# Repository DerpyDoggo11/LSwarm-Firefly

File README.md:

# LSwarm Firefly
A single motor Micro-Aerial Vehicle for drone swarm light displays

## Case

## 3D PCB Preview

## PCB Wiring

## PCB Schematic

### Download ./latestProduction to fabricate your own PCB.

## Introduction
The LS Firefly is the baby brother to the original [LS Mk.1](https://github.com/DerpyDoggo11/LSwarm), the goal is to be smaller, safer, and a little more unique than the previous drone. Although it does come at some costs such as reduced manuverability and no USB-C connectivity. Like the previous model, rather than using GPS, it uses UWB frequencies to communicate with ground anchors (see [LS Anchor](https://github.com/DerpyDoggo11/LSwarm-Anchor)) for positioning. To fabricate these drones yourself, see the bill of materials below and follow the instructions. 

Note: this drone is all open sourced under the GNU GPL license! (do what you will with the code and designs but make sure to keep it open-source! :D)

### Are drone swarms legal in the US?
TLDR: yes and no, mostly no but sometimes yes. 

In the US, flying more than one drone by yourself outside is technically not legal without a permit, but flying indoors (or under some netting outside) is perfectly allowed, so make sure you understand this before buying or assembling any components.

If you live outside of the US, the restrictions will be different so make sure you check with your local government. 

## Bill of Materials 

### (Minimum build for testing: 5 drones)

| Quantity | Components | Price | Link |
|--------- |----------|----------| -----|
| 5  | Brushless Motors | ~$56.27  | [here](https://www.aliexpress.us/item/3256811751884831.html?spm=a2g0o.productlist.main.5.4bc27ec1sXcpi9&algo_pvid=f93d3c7b-d188-41d3-8071-ca4f01f3da9e&algo_exp_id=f93d3c7b-d188-41d3-8071-ca4f01f3da9e-4&pdp_ext_f=%7B%22order%22%3A%2244%22%2C%22eval%22%3A%221%22%2C%22fromPage%22%3A%22search%22%7D&pdp_npi=6%40dis%21USD%2127.91%2112.75%21%21%2127.91%2112.75%21%402103129f17839010468456329ea712%2112000057077353974%21sea%21US%217493938711%21X%211%210%21n_tag%3A-29919%3Bd%3Ad260408f%3Bm03_new_user%3A-29895%3BpisId%3A5000000204411062&curPageLogUid=VGuc6eNMjhlE&utparam-url=scene%3Asearch%7Cquery_from%3A%7Cx_object_id%3A1005011938199583%7C_p_origin_prod%3A#nav-review)
| 5 | 65mm Propellers (1.5mm hole) | $2.42 | [here](https://www.aliexpress.us/item/3256808528649872.html?spm=a2g0o.productlist.main.1.b0be6fedKhbLdF&algo_pvid=3254f102-23a3-44f5-862f-50a3a50c42db&algo_exp_id=3254f102-23a3-44f5-862f-50a3a50c42db-0&pdp_ext_f=%7B%22order%22%3A%2263%22%2C%22eval%22%3A%221%22%2C%22fromPage%22%3A%22search%22%7D&pdp_npi=6%40dis%21USD%213.73%210.99%21%21%213.73%210.99%21%402101e80f17839019729517303e1028%2112000046361007970%21sea%21US%217493938711%21X%211%210%21n_tag%3A-29919%3Bd%3Ad260408f%3Bm03_new_user%3A-29895%3BpisId%3A5000000204411062&curPageLogUid=khfzd3PNDSbd&utparam-url=scene%3Asearch%7Cquery_from%3A%7Cx_object_id%3A1005008714964624%7C_p_origin_prod%3A) 
| 10  | 1s 300mAh Battery | ~$19.75 | [here](https://www.aliexpress.us/item/3256801127609470.html?spm=a2g0o.productlist.main.8.43a2a5M9a5M9yu&aem_p4p_detail=202607121047491621817576276750009408507&algo_pvid=07c6ddd0-7cad-4da9-88c7-c570960c9574&algo_exp_id=07c6ddd0-7cad-4da9-88c7-c570960c9574-7&pdp_ext_f=%7B%22order%22%3A%22137%22%2C%22eval%22%3A%221%22%2C%22fromPage%22%3A%22search%22%7D&pdp_npi=6%40dis%21USD%214.71%213.30%21%21%2131.79%2122.25%21%40210319b017838784692687812e95b8%2112000015664187048%21sea%21US%217493938711%21X%211%210%21n_tag%3A-29919%3Bd%3Ad260408f%3Bm03_new_user%3A-29895&curPageLogUid=hyAg3GWOKWbh&utparam-url=scene%3Asearch%7Cquery_from%3A%7Cx_object_id%3A1005001313924222%7C_p_origin_prod%3A&search_p4p_id=202607121047491621817576276750009408507_2) 
|5 | 2.4G Wifi Antennas | ~$3.52 | [here](https://www.aliexpress.us/item/3256802833801038.html?spm=a2g0o.productlist.main.17.44bbCrBdCrBdFl&algo_pvid=20d56933-2b0c-45d5-8601-1bc6a9682401&algo_exp_id=20d56933-2b0c-45d5-8601-1bc6a9682401-16&pdp_ext_f=%7B%22order%22%3A%221074%22%2C%22eval%22%3A%221%22%2C%22fromPage%22%3A%22search%22%7D&pdp_npi=6%40dis%21USD%213.55%213.52%21%21%213.55%213.52%21%402101ef5e17781321493642302e40a6%2112000023272348781%21sea%21US%217493938711%21X%211%210%21n_tag%3A-29913%3Bd%3A21b1ce8d%3Bm03_new_user%3A-29895&curPageLogUid=rLnZuf4b98Bi&utparam-url=scene%3Asearch%7Cquery_from%3A%7Cx_object_id%3A1005003020115790%7C_p_origin_prod%3A)
| 5  | LS Firefly PCBs | ~$25 (with shipping, cost can vary widely however) | Download repo, extract fabrication files, and fabricate pcb through JLCPCB, purchase components from LCSC (complete instructions for this may come soon)
| 5  | Electronics | ~$125 (with shipping, cost can vary widely however) | Purchase components from LCSC

Total cost: **$231,96**

Cost per drone: **$46.39**

## Tools / Other parts:
- Hot-air reflow station or SMD hot plate
- Soldering iron + solder
- Solder paste for SMD components
- Tweezers for SMD components

For drone light displays, you'll also need the [UWB anchors](https://github.com/DerpyDoggo11/LSwarm-Anchor) and a powerful MCU devboard or laptop.

## Assembly:
1. Apply solder paste to all smd components directly or through a stencil
2. Heat up components with a hot plate or hot-air gun
3. 3D print drone case
4. Mount components to drone case
4. Plug in USB-C port and upload software

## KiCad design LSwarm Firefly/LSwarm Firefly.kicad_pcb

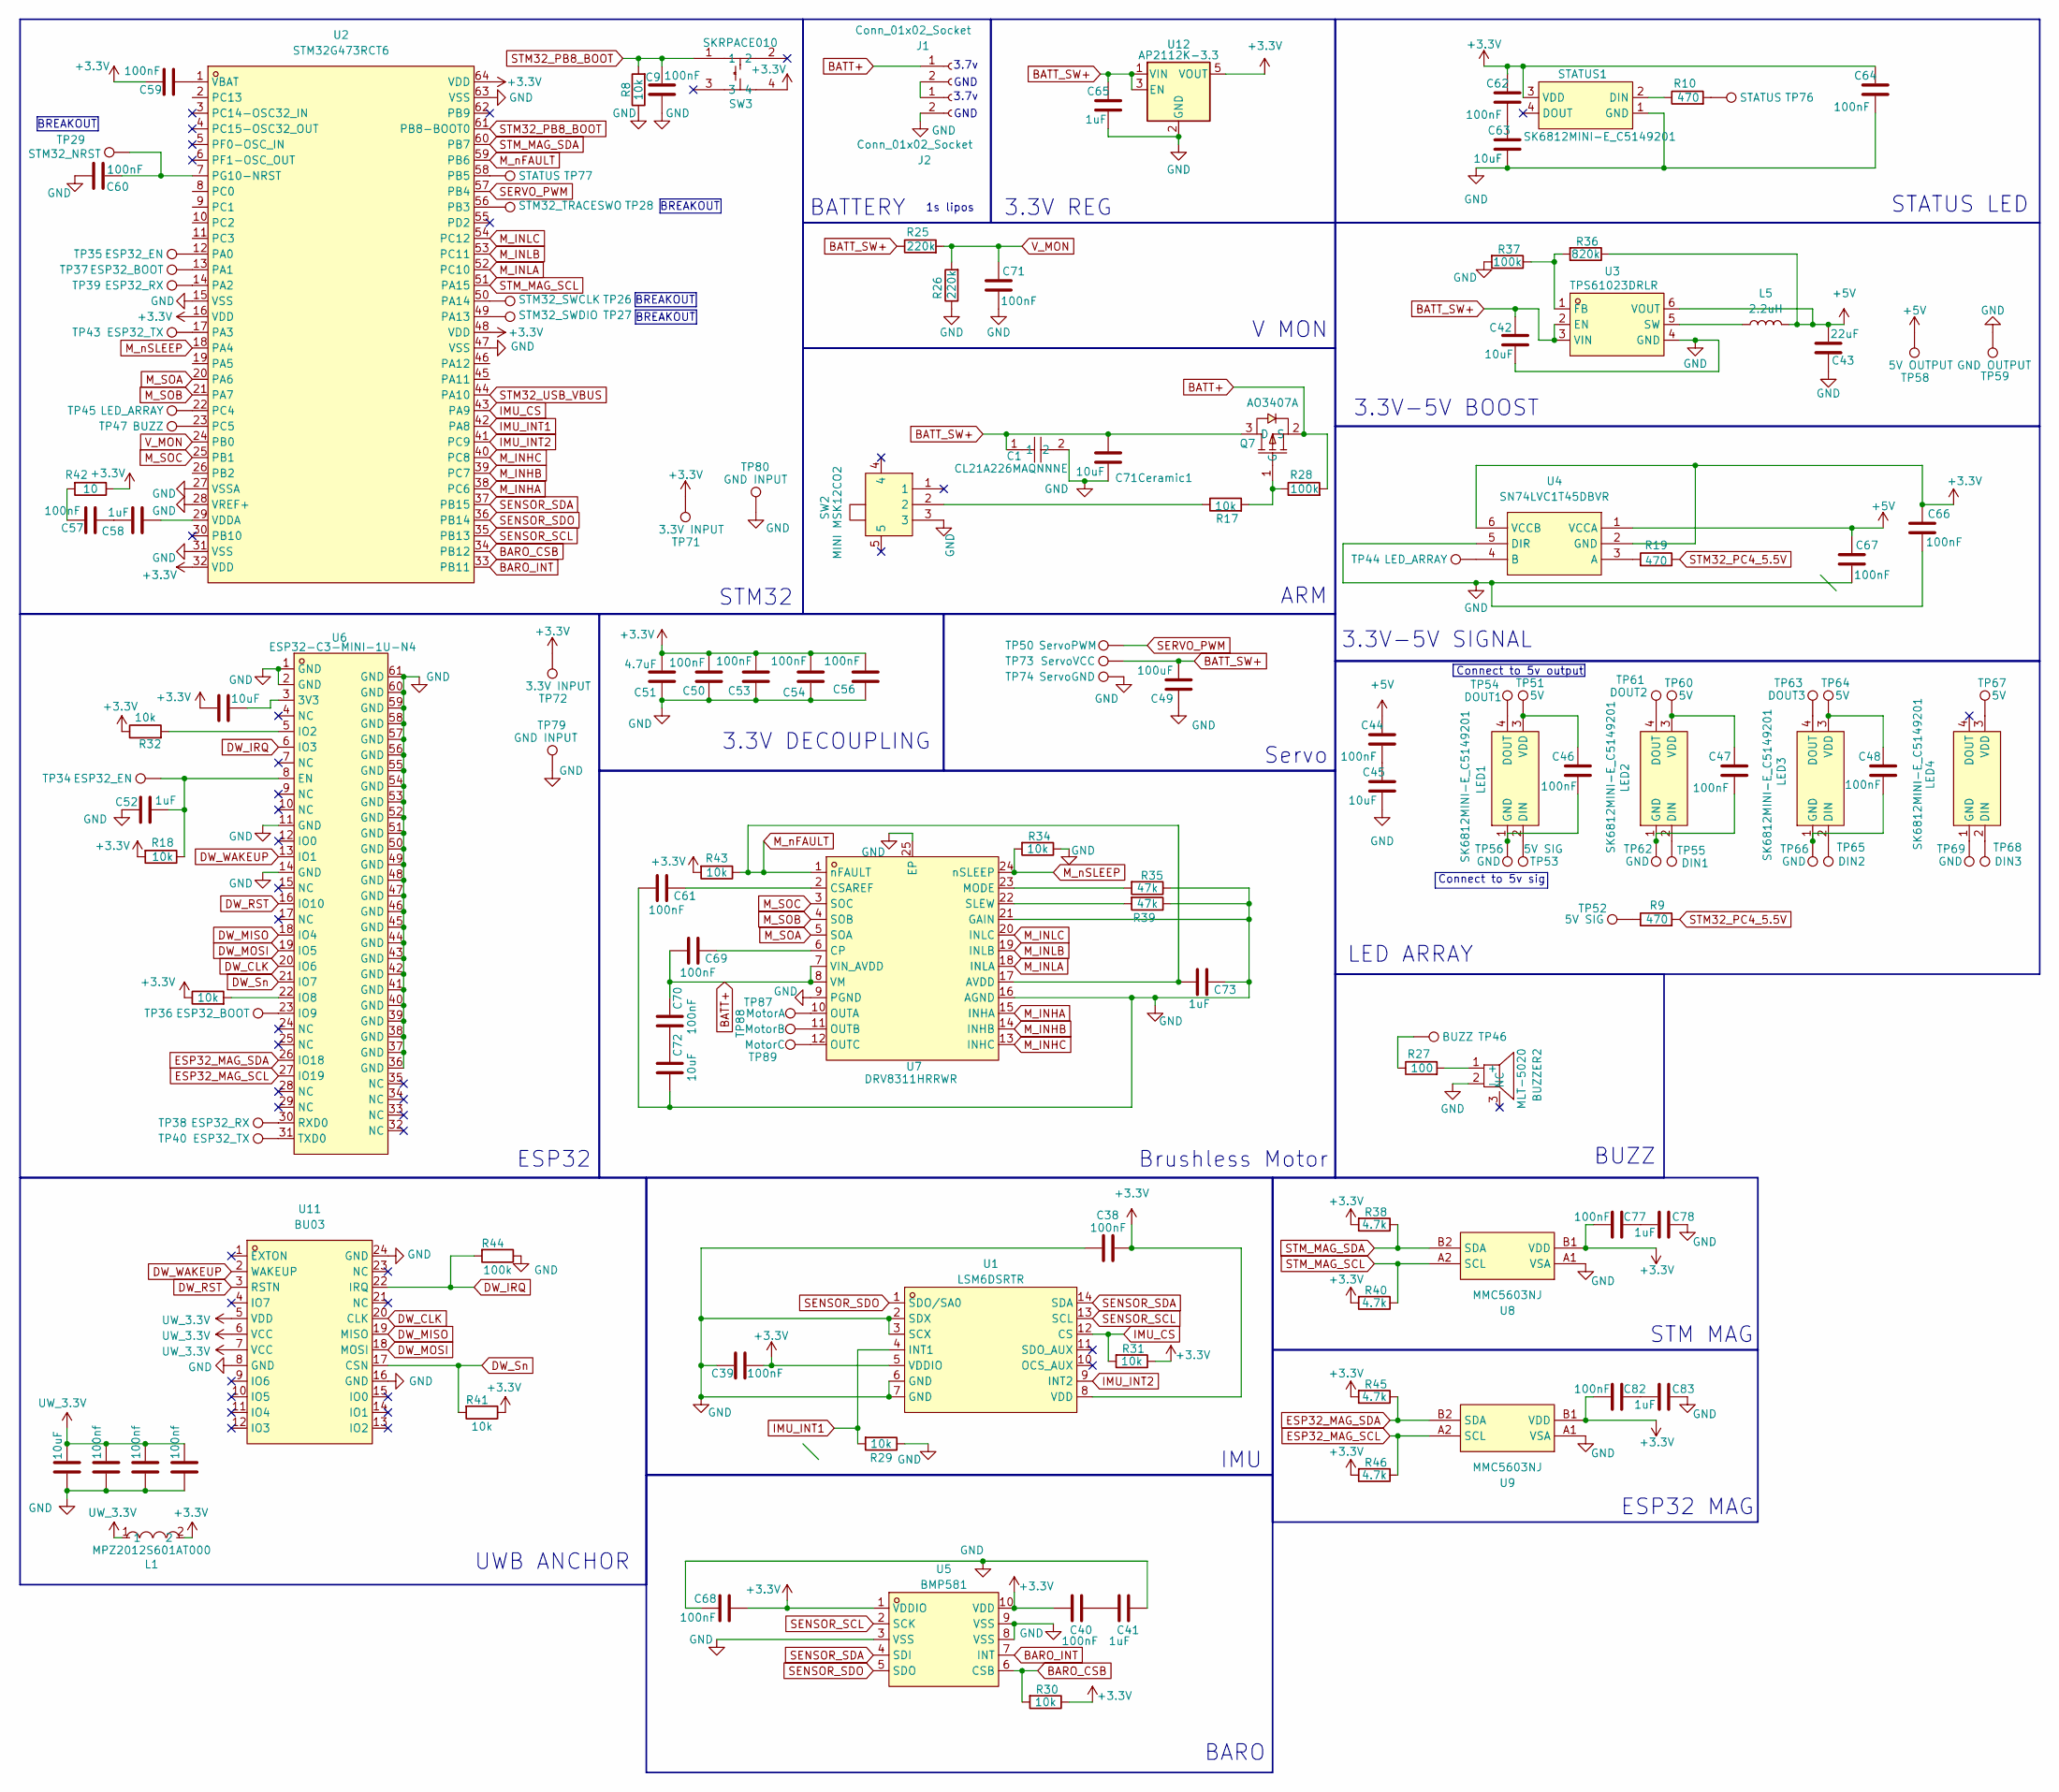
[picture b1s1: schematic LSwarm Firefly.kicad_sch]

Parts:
BUZZER2: MLT-5020; BUZ-SMD_L5.0-W5.5-P4.60; MPN MLT-5020; LCSC Part C94598
C1: CL21A226MAQNNNE; C0805; MPN CL21A226MAQNNNE; LCSC Part C45783
C9, C38, C39, C40, C44, C46, C47, C48, C50, C53, C54, C56, C57, C59, C60, C61, C62, C64, C66, C67, C68, C69, C70, C71, C77, C82: 100nF; C_0603_1608Metric
C41, C52, C58, C65, C73, C78, C83: 1uF; C_0603_1608Metric
C42, C45, C63, C71Ceramic1: 10uF; C_0805_2012Metric
C43: 22uF; C_0805_2012Metric
C49: 100uF; C_0603_1608Metric
C51: 4.7uF; C_0603_1608Metric
C55, C72, C76: 10uF; C_0603_1608Metric
C79, C80, C81: 100nf; C_0603_1608Metric
J1, J2: Conn_01x02_Socket; PinHeader_1x02_P1.00mm_Vertical
L1: MPZ2012S601AT000; L0805; MPN MPZ2012S601AT000; LCSC Part C21519
L5: 2.2uH; L_1210_3225Metric
LED1, LED2, LED3, LED4: SK6812MINI-E_C5149201; LED-SMD_4P-L3.2-W2.8-LS5.9_SK6812MINI-E; MPN SK6812MINI-E; LCSC Part C5149201
Q7: AO3407A; SOT-23-3_L2.9-W1.6-P1.90-LS2.8-BR; MPN AO3407A; LCSC Part C15155
R8, R17, R18, R29, R30, R31, R32, R33, R34, R41, R43: 10k; R_0603_1608Metric
R9, R10, R19: 470; R_0603_1608Metric
R25, R26: 220k; R_0603_1608Metric
R27: 100; R_0603_1608Metric
R28, R37, R44: 100k; R_0603_1608Metric
R35, R39: 47k; R_0603_1608Metric
R36: 820k; R_0603_1608Metric
R38, R40, R45, R46: 4.7k; R_0603_1608Metric
R42: 10; R_0603_1608Metric
STATUS1: SK6812MINI-E_C5149201; LED-SMD_4P-L3.2-W2.8-LS5.9_SK6812MINI-E; MPN SK6812MINI-E; LCSC Part C5149201
SW2: MINI MSK12CO2; SW-SMD_MSK12CO2; MPN MINI MSK12CO2; LCSC Part C2681570
SW3: SKRPACE010; KEY-SMD_4P-L4.2-W3.2-P2.20-LS4.6; MPN SKRPACE010; LCSC Part C139797
TP26: STM32_SWCLK; TestPoint_Pad_1.0x1.0mm
TP27: STM32_SWDIO; TestPoint_Pad_1.0x1.0mm
TP28: STM32_TRACESWO; TestPoint_Pad_1.0x1.0mm
TP29: STM32_NRST; TestPoint_Pad_1.0x1.0mm
TP34, TP35: ESP32_EN; TestPoint_Pad_1.0x1.0mm
TP36, TP37: ESP32_BOOT; TestPoint_Pad_1.0x1.0mm
TP38, TP39: ESP32_RX; TestPoint_Pad_1.0x1.0mm
TP40, TP43: ESP32_TX; TestPoint_Pad_1.0x1.0mm
TP44, TP45: LED_ARRAY; TestPoint_Pad_1.0x1.0mm
TP46, TP47: BUZZ; TestPoint_Pad_1.0x1.0mm
TP50: ServoPWM; TestPoint_Pad_1.0x1.0mm
TP51, TP60, TP64, TP67: 5V; TestPoint_Pad_1.0x1.0mm
TP52, TP53: 5V SIG; TestPoint_Pad_1.0x1.0mm
TP54: DOUT1; TestPoint_Pad_1.0x1.0mm
TP55: DIN1; TestPoint_Pad_1.0x1.0mm
TP56, TP62, TP66, TP69: GND; TestPoint_Pad_1.0x1.0mm
TP58: 5V OUTPUT; TestPoint_Pad_1.0x1.0mm
TP59: GND OUTPUT; TestPoint_Pad_1.0x1.0mm
TP61: DOUT2; TestPoint_Pad_1.0x1.0mm
TP63: DOUT3; TestPoint_Pad_1.0x1.0mm
TP65: DIN2; TestPoint_Pad_1.0x1.0mm
TP68: DIN3; TestPoint_Pad_1.0x1.0mm
TP71, TP72: 3.3V INPUT; TestPoint_Pad_1.0x1.0mm
TP73: ServoVCC; TestPoint_Pad_1.0x1.0mm
TP74: ServoGND; TestPoint_Pad_1.0x1.0mm
TP76, TP77: STATUS; TestPoint_Pad_1.0x1.0mm
TP79, TP80: GND INPUT; TestPoint_Pad_1.0x1.0mm
TP87: MotorA; TestPoint_Pad_1.0x1.0mm
TP88: MotorB; TestPoint_Pad_1.0x1.0mm
TP89: MotorC; TestPoint_Pad_1.0x1.0mm
U1: LSM6DSRTR; LGA-14_L3.0-W2.5-P0.50-BR; MPN LSM6DSRTR; LCSC Part C784817
U2: STM32G473RCT6; LQFP-64_L10.0-W10.0-P0.50-LS12.0-BL; MPN STM32G473RCT6; LCSC Part C529361
U3: TPS61023DRLR; SOT-563_L1.6-W1.2-P0.50-LS1.6-BR; MPN TPS61023DRLR; LCSC Part C919459
U4: SN74LVC1T45DBVR; SOT-23-6_L2.9-W1.6-P0.95-LS2.8-BR; MPN SN74LVC1T45DBVR; LCSC Part C7843
U5: BMP581; LGA-10_L2.0-W2.0-P0.50-TL_BMP581; MPN BMP581; LCSC Part C5362283
U6: ESP32-C3-MINI-1U-N4; WIFIM-SMD_61P-L13.2-W12.5-P0.80; MPN ESP32-C3-MINI-1U-N4; LCSC Part C2911374
U7: DRV8311HRRWR; QFN-24_L3.0-W3.0-P0.40-TL-EP1.9_TI_RRW0024A; MPN DRV8311HRRWR; LCSC Part C5218862
U8, U9: MMC5603NJ; FLIPCHIP-4_L0.8-W0.8-R2-C2-P0.40-TL; MPN MMC5603NJ; LCSC Part C404328
U11: BU03; WIRELM-SMD_BU03; MPN BU03; LCSC Part C42419011
U12: AP2112K-3.3; SOT-23-5

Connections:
+3.3V: C38.1, C39.1, C40.2, C50.2, C51.2, C53.2, C54.2, C55.2, C56.2, C59.1, C62.2, C64.2, C66.2, C68.1, C77.1, C82.1, L1.2, R18.2, R30.1, R31.1, R32.1, R33.1, R38.2, R40.2, R41.1, R42.1, R43.2, R45.2, R46.2, STATUS1.3 (VDD), SW3.4, TP71.1 (1_1), TP72.1 (1_1), U1.5 (VDDIO), U1.8 (VDD), U2.16 (VDD), U2.32 (VDD), U2.48 (VDD), U2.64 (VDD), U4.2 (GND), U4.6 (VCCB), U5.1 (VDDIO), U5.10 (VDD), U8.B1 (VDD), U9.B1 (VDD), U12.5 (VOUT)
+5V: C43.2, C44.2, C67.2, L5.2, R36.1, TP58.1 (1_1), U3.6 (VOUT), U4.1 (VCCA)
BARO_CSB: R30.2, U2.34 (PB12), U5.6 (CSB)
BARO_INT: U2.33 (PB11), U5.7 (INT)
BATT+: C69.2, C70.1, J1.1, Q7.2 (S), R28.2, U7.7 (VIN_AVDD), U7.8 (VM)
BATT_SW+: C1.1, C42.1, C49.2, C65.2, C71Ceramic1.2, Q7.3 (D), R25.1, TP73.1 (1_1), U3.2 (EN), U3.3 (VIN), U12.1 (VIN), U12.3 (EN)
DW_CLK: U6.20 (IO6), U11.20 (CLK)
DW_IRQ: R44.2, U6.6 (IO3), U11.22 (IRQ)
DW_MISO: U6.18 (IO4), U11.19 (MISO)
DW_MOSI: U6.19 (IO5), U11.18 (MOSI)
DW_RST: U6.16 (IO10), U11.3 (RSTN)
DW_Sn: R41.2, U6.21 (IO7), U11.17 (CSN)
DW_WAKEUP: U6.13 (IO1), U11.2 (WAKEUP)
ESP32_MAG_SCL: R46.1, U6.27 (IO19), U9.A2 (SCL)
ESP32_MAG_SDA: R45.1, U6.26 (IO18), U9.B2 (SDA)
GND: BUZZER2.2 (-), C1.2, C9.2, C38.2, C39.2, C41.1, C42.2, C43.1, C45.1, C49.1, C50.1, C51.1, C52.1, C53.1, C54.1, C56.1, C60.1, C61.2, C63.1, C64.1, C65.1, C66.1, C67.1, C68.2, C71.1, C71Ceramic1.1, C72.2, C73.1, C76.2, C78.2, C79.2, C80.2, C81.2, C83.2, J2.2, R8.1, R26.1, R29.1, R34.1, R35.1, R37.2, R39.1, R44.1, STATUS1.1 (GND), SW2.3, TP59.1 (1_1), TP74.1 (1_1), TP79.1 (1_1), TP80.1 (1_1), U1.2 (SDX), U1.3 (SCX), U1.6 (GND), U1.7 (GND), U2.15 (VSS), U2.27 (VSSA), U2.28 (VREF+), U2.31 (VSS), U2.47 (VSS), U2.63 (VSS), U3.4 (GND), U4.5 (DIR), U5.3 (VSS), U5.8 (VSS), U5.9 (VSS), U6.1 (GND), U6.2 (GND), U6.11 (GND), U6.14 (GND), U6.36 (GND), U6.37 (GND), U6.38 (GND), U6.39 (GND), U6.40 (GND), U6.41 (GND), U6.42 (GND), U6.43 (GND), U6.44 (GND), U6.45 (GND), U6.46 (GND), U6.47 (GND), U6.48 (GND), U6.49 (GND), U6.50 (GND), U6.51 (GND), U6.52 (GND), U6.53 (GND), U6.54 (GND), U6.55 (GND), U6.56 (GND), U6.57 (GND), U6.58 (GND), U6.59 (GND), U6.60 (GND), U6.61 (GND), U7.9 (PGND), U7.16 (AGND), U7.21 (GAIN), U7.25 (EP), U8.A1 (VSA), U9.A1 (VSA), U11.8 (GND), U11.16 (GND), U11.24 (GND), U12.2 (GND)
IMU_CS: R31.2, U1.12 (CS), U2.43 (PA9)
IMU_INT1: R29.2, U1.4 (INT1), U2.42 (PA8)
IMU_INT2: U1.9 (INT2), U2.41 (PC9)
M_INHA: U2.38 (PC6), U7.15 (INHA)
M_INHB: U2.39 (PC7), U7.14 (INHB)
M_INHC: U2.40 (PC8), U7.13 (INHC)
M_INLA: U2.52 (PC10), U7.18 (INLA)
M_INLB: U2.53 (PC11), U7.19 (INLB)
M_INLC: U2.54 (PC12), U7.20 (INLC)
M_SOA: U2.20 (PA6), U7.5 (SOA)
M_SOB: U2.21 (PA7), U7.4 (SOB)
M_SOC: U2.25 (PB1), U7.3 (SOC)
M_nFAULT: C73.2, R43.1, U2.59 (PB6), U7.1 (nFAULT), U7.17 (AVDD)
M_nSLEEP: R34.2, U2.18 (PA4), U7.24 (nSLEEP)
unnamed: BUZZER2.1 (+), R27.2
unnamed: C40.1, C41.2
unnamed: C44.1, C45.2
unnamed: C57.1, R42.2
unnamed: C57.2, C58.1
unnamed: C62.1, C63.2
unnamed: C70.2, C72.1
unnamed: C77.2, C78.1
unnamed: C82.2, C83.1
unnamed: J1.2, J2.1
unnamed: LED1.2 (DIN), TP53.1 (1_1)
unnamed: LED1.4 (DOUT), TP54.1 (1_1)
unnamed: C46.1, LED1.1 (GND), TP56.1 (1_1)
unnamed: C46.2, LED1.3 (VDD), TP51.1 (1_1)
unnamed: LED2.2 (DIN), TP55.1 (1_1)
unnamed: LED2.4 (DOUT), TP61.1 (1_1)
unnamed: C47.1, LED2.1 (GND), TP62.1 (1_1)
unnamed: C47.2, LED2.3 (VDD), TP60.1 (1_1)
unnamed: LED3.2 (DIN), TP65.1 (1_1)
unnamed: LED3.4 (DOUT), TP63.1 (1_1)
unnamed: C48.1, LED3.1 (GND), TP66.1 (1_1)
unnamed: C48.2, LED3.3 (VDD), TP64.1 (1_1)
unnamed: LED4.2 (DIN), TP68.1 (1_1)
unnamed: LED4.1 (GND), TP69.1 (1_1)
unnamed: LED4.3 (VDD), TP67.1 (1_1)
unnamed: Q7.1 (G), R17.2, R28.1
unnamed: R9.1, TP52.1 (1_1)
unnamed: R10.2, TP76.1 (1_1)
unnamed: R17.1, SW2.2
unnamed: R27.1, TP46.1 (1_1)
unnamed: R10.1, STATUS1.2 (DIN)
unnamed: TP35.1 (1_1), U2.12 (PA0)
unnamed: TP37.1 (1_1), U2.13 (PA1)
unnamed: TP39.1 (1_1), U2.14 (PA2)
unnamed: TP43.1 (1_1), U2.17 (PA3)
unnamed: TP27.1 (1_1), U2.49 (PA13)
unnamed: TP26.1 (1_1), U2.50 (PA14)
unnamed: TP28.1 (1_1), U2.56 (PB3)
unnamed: TP77.1 (1_1), U2.58 (PB5)
unnamed: TP45.1 (1_1), U2.22 (PC4)
unnamed: TP47.1 (1_1), U2.23 (PC5)
unnamed: C60.2, TP29.1 (1_1), U2.7 (PG10-NRST)
unnamed: C59.2, U2.1 (VBAT)
unnamed: C58.2, U2.29 (VDDA)
unnamed: R36.2, R37.1, U3.1 (FB)
unnamed: L5.1, U3.5 (SW)
unnamed: R19.2, U4.3 (A)
unnamed: TP44.1 (1_1), U4.4 (B)
unnamed: C55.1, U6.3 (3V3)
unnamed: C52.2, R18.1, TP34.1 (1_1), U6.8 (EN)
unnamed: R32.2, U6.5 (IO2)
unnamed: R33.2, U6.22 (IO8)
unnamed: TP36.1 (1_1), U6.23 (IO9)
unnamed: TP38.1 (1_1), U6.30 (RXD0)
unnamed: TP40.1 (1_1), U6.31 (TXD0)
unnamed: C69.1, U7.6 (CP)
unnamed: C61.1, U7.2 (CSAREF)
unnamed: R35.2, U7.23 (MODE)
unnamed: TP87.1 (1_1), U7.10 (OUTA)
unnamed: TP88.1 (1_1), U7.11 (OUTB)
unnamed: TP89.1 (1_1), U7.12 (OUTC)
unnamed: R39.2, U7.22 (SLEW)
SENSOR_SCL: U1.13 (SCL), U2.35 (PB13), U5.2 (SCK)
SENSOR_SDA: U1.14 (SDA), U2.37 (PB15), U5.4 (SDI)
SENSOR_SDO: U1.1 (SDO/SA0), U2.36 (PB14), U5.5 (SDO)
SERVO_PWM: TP50.1 (1_1), U2.57 (PB4)
STM32_PB8_BOOT: C9.1, R8.2, SW3.1, U2.61 (PB8-BOOT0)
STM32_PC4_5.5V: R9.2, R19.1
STM32_USB_VBUS: U2.44 (PA10)
STM_MAG_SCL: R40.1, U2.51 (PA15), U8.A2 (SCL)
STM_MAG_SDA: R38.1, U2.60 (PB7), U8.B2 (SDA)
UW_3.3V: C76.1, C79.1, C80.1, C81.1, L1.1, U11.5 (VDD), U11.6 (VCC), U11.7 (VCC)
V_MON: C71.2, R25.2, R26.2, U2.24 (PB0)

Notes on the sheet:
3.3V DECOUPLING
3.3V REG
BUZZ
BREAKOUT
GND
Connect to 5v output
Connect to 5v sig
STM32
STM MAG
3.7v
ESP32 MAG
BARO
1s lipos
ARM
Brushless Motor
3.3V-5V SIGNAL
3.3V-5V BOOST
LED ARRAY
Servo
V MON
STATUS LED
ESP32
UWB ANCHOR
BATTERY
IMU

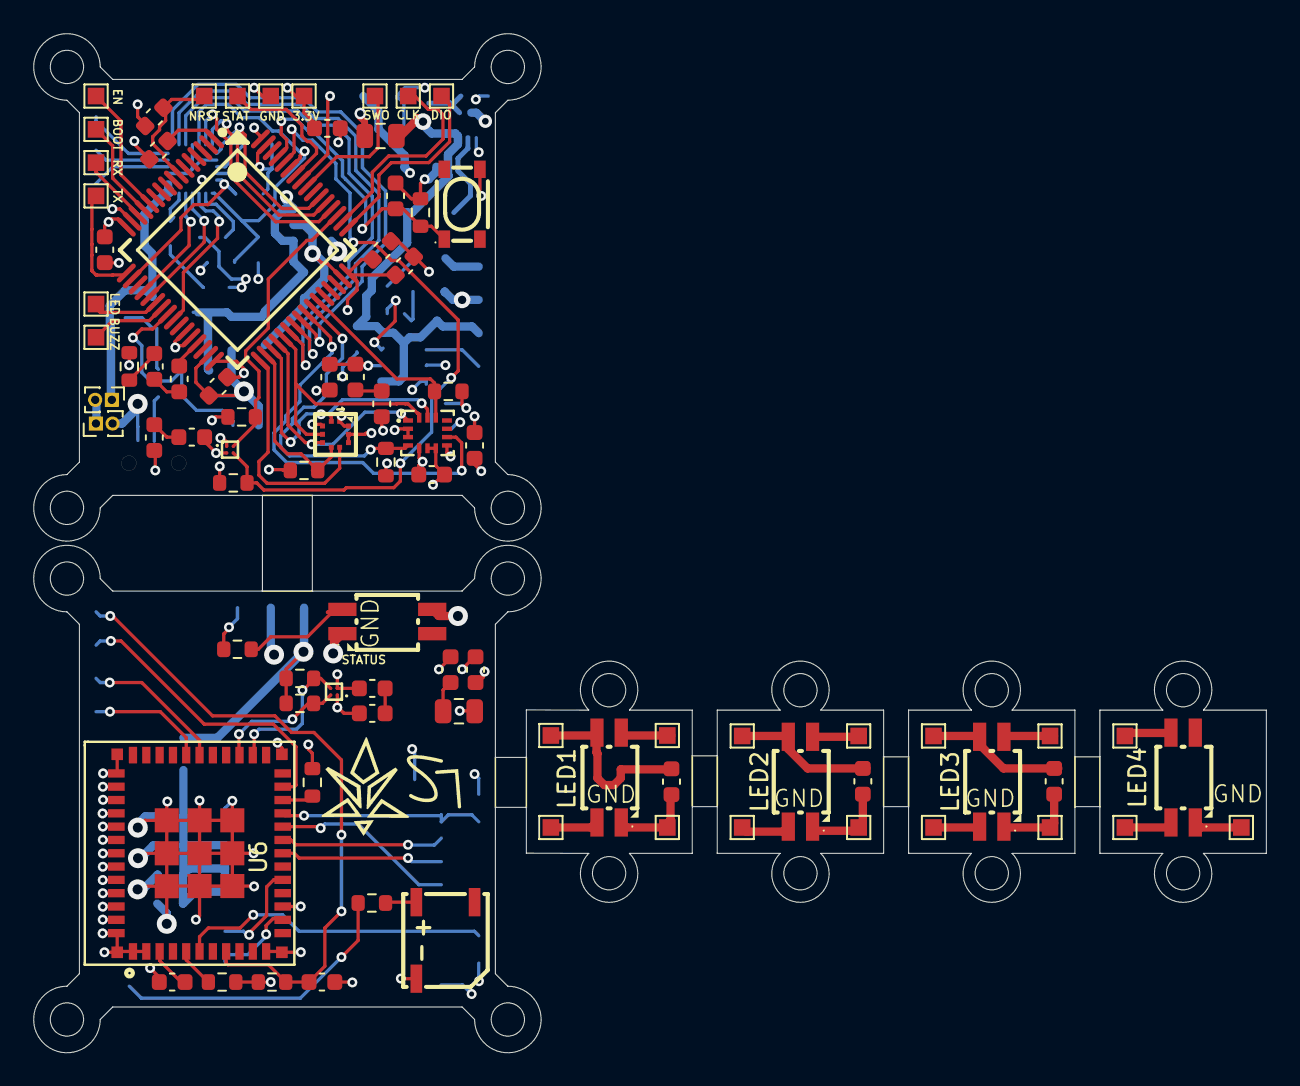
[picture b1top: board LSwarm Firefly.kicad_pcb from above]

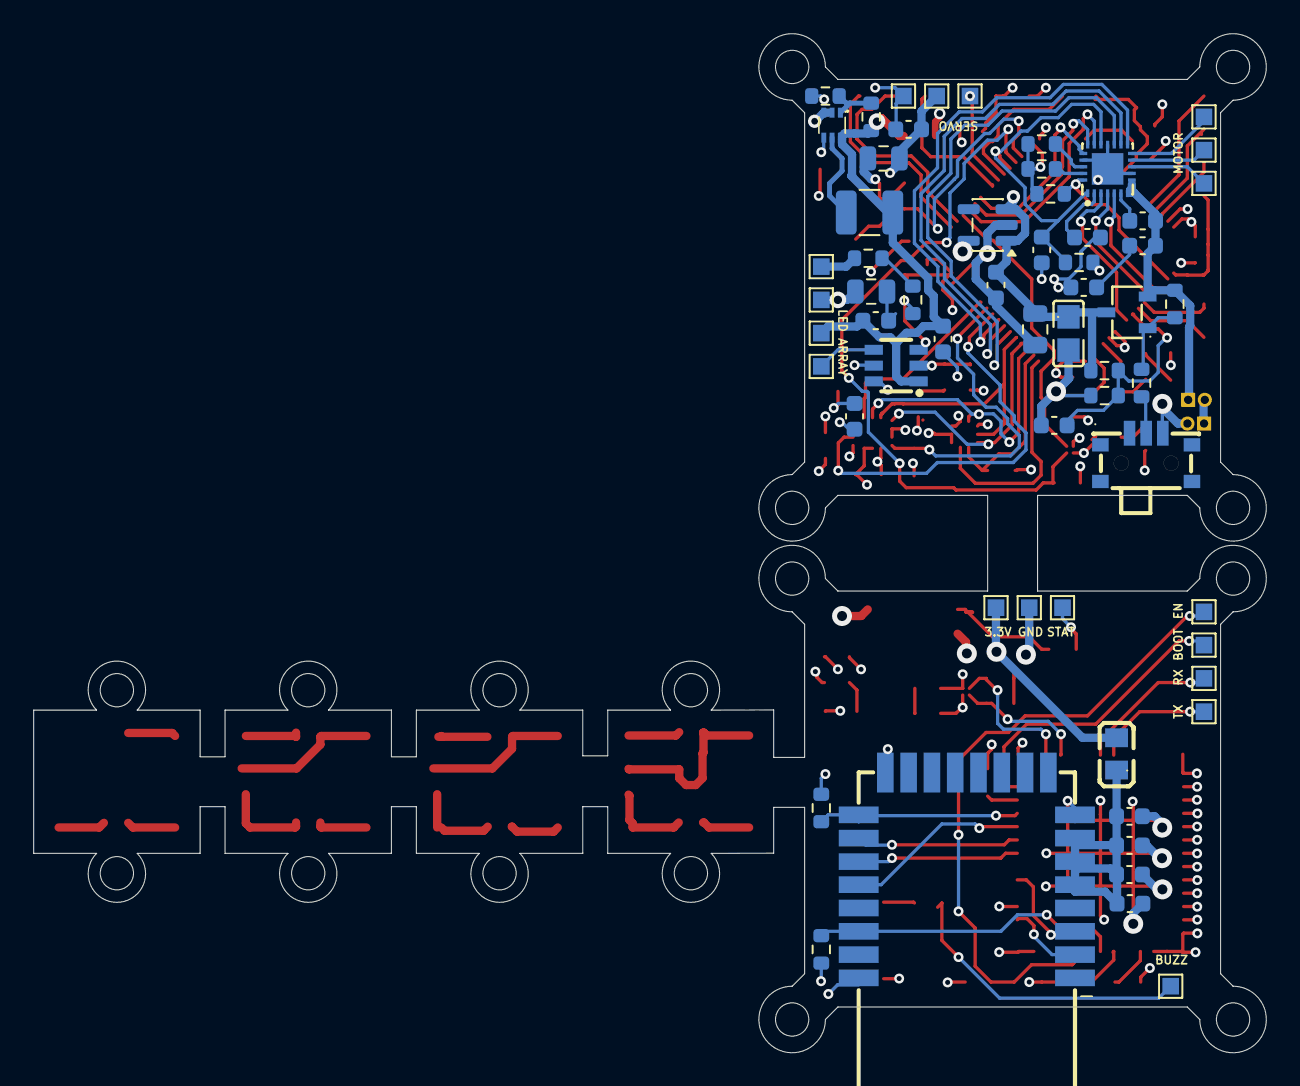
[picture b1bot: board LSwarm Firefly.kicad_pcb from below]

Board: 4 copper layers, 74.1 x 61.2 mm, 145 parts (60 on the bottom side), 102 nets.

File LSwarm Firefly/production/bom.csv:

Designator,Footprint,Quantity,Value,LCSC Part #
BUZZER2,BUZ-SMD_L5.0-W5.5-P4.60,1,MLT-5020,C94598
C1,C0805,1,CL21A226MAQNNNE,C45783
"C38, C39, C40, C44, C46, C47, C48, C50, C53, C54, C56, C57, C59, C60, C61, C62, C64, C66, C67, C68, C69, C70, C71, C77, C79, C80, C81, C82, C9",0603,29,100nF,
"C41, C52, C58, C65, C73, C78, C83",0603,7,1uF,
"C42, C45, C63, C71CERAMIC1",0805,4,10uF,
C43,0805,1,22uF,
C49,0603,1,100uF,
C51,0603,1,4.7uF,
"C55, C72, C76",0603,3,10uF,
"J1, J2",PinHeader_1x02_P1.00mm_Vertical,2,Conn_01x02_Socket,
L1,L0805,1,MPZ2012S601AT000,C21519
L5,1210,1,2.2uH,
"LED1, LED2, LED3, LED4, STATUS1",LED-SMD_4P-L3.2-W2.8-LS5.9_SK6812MINI-E,5,SK6812MINI-E_C5149201,C5149201
Q7,SOT-23-3_L2.9-W1.6-P1.90-LS2.8-BR,1,AO3407A,C15155
"R10, R19, R9",0603,3,470,
"R17, R18, R29, R30, R31, R32, R33, R34, R41, R43, R8",0603,11,10k,
"R25, R26",0603,2,220k,
R27,0603,1,100,
"R28, R37, R44",0603,3,100k,
"R35, R39",0603,2,47k,
R36,0603,1,820k,
"R38, R40, R45, R46",0603,4,4.7k,
R42,0603,1,10,
SW2,SW-SMD_MSK12CO2,1,MINI MSK12CO2,C2681570
SW3,KEY-SMD_4P-L4.2-W3.2-P2.20-LS4.6,1,SKRPACE010,C139797
TP26,TestPoint_Pad_1.0x1.0mm,1,STM32_SWCLK,
TP27,TestPoint_Pad_1.0x1.0mm,1,STM32_SWDIO,
TP28,TestPoint_Pad_1.0x1.0mm,1,STM32_TRACESWO,
TP29,TestPoint_Pad_1.0x1.0mm,1,STM32_NRST,
"TP34, TP35",TestPoint_Pad_1.0x1.0mm,2,ESP32_EN,
"TP36, TP37",TestPoint_Pad_1.0x1.0mm,2,ESP32_BOOT,
"TP38, TP39",TestPoint_Pad_1.0x1.0mm,2,ESP32_RX,
"TP40, TP43",TestPoint_Pad_1.0x1.0mm,2,ESP32_TX,
"TP44, TP45",TestPoint_Pad_1.0x1.0mm,2,LED_ARRAY,
"TP46, TP47",TestPoint_Pad_1.0x1.0mm,2,BUZZ,
TP50,TestPoint_Pad_1.0x1.0mm,1,ServoPWM,
"TP51, TP60, TP64, TP67",TestPoint_Pad_1.0x1.0mm,4,5V,
"TP52, TP53",TestPoint_Pad_1.0x1.0mm,2,5V SIG,
TP54,TestPoint_Pad_1.0x1.0mm,1,DOUT1,
TP55,TestPoint_Pad_1.0x1.0mm,1,DIN1,
"TP56, TP62, TP66, TP69",TestPoint_Pad_1.0x1.0mm,4,GND,
TP58,TestPoint_Pad_1.0x1.0mm,1,5V OUTPUT,
TP59,TestPoint_Pad_1.0x1.0mm,1,GND OUTPUT,
TP61,TestPoint_Pad_1.0x1.0mm,1,DOUT2,
TP63,TestPoint_Pad_1.0x1.0mm,1,DOUT3,
TP65,TestPoint_Pad_1.0x1.0mm,1,DIN2,
TP68,TestPoint_Pad_1.0x1.0mm,1,DIN3,
"TP71, TP72",TestPoint_Pad_1.0x1.0mm,2,3.3V INPUT,
TP73,TestPoint_Pad_1.0x1.0mm,1,ServoVCC,
TP74,TestPoint_Pad_1.0x1.0mm,1,ServoGND,
"TP76, TP77",TestPoint_Pad_1.0x1.0mm,2,STATUS,
"TP79, TP80",TestPoint_Pad_1.0x1.0mm,2,GND INPUT,
TP87,TestPoint_Pad_1.0x1.0mm,1,MotorA,
TP88,TestPoint_Pad_1.0x1.0mm,1,MotorB,
TP89,TestPoint_Pad_1.0x1.0mm,1,MotorC,
U1,LGA-14_L3.0-W2.5-P0.50-BR,1,LSM6DSRTR,C784817
U11,WIRELM-SMD_BU03,1,BU03,C42419011
U12,SOT-23-5,1,AP2112K-3.3,
U2,LQFP-64_L10.0-W10.0-P0.50-LS12.0-BL,1,STM32G473RCT6,C529361
U3,SOT-563_L1.6-W1.2-P0.50-LS1.6-BR,1,TPS61023DRLR,C919459
U4,SOT-23-6_L2.9-W1.6-P0.95-LS2.8-BR,1,SN74LVC1T45DBVR,C7843
U5,LGA-10_L2.0-W2.0-P0.50-TL_BMP581,1,BMP581,C5362283
U6,WIFIM-SMD_61P-L13.2-W12.5-P0.80,1,ESP32-C3-MINI-1U-N4,C2911374
U7,QFN-24_L3.0-W3.0-P0.40-TL-EP1.9_TI_RRW0024A,1,DRV8311HRRWR,C5218862
"U8, U9",FLIPCHIP-4_L0.8-W0.8-R2-C2-P0.40-TL,2,MMC5603NJ,C404328

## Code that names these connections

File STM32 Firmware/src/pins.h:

#pragma once
#include <Arduino.h>


// ESP32
#define PIN_ESP_EN PA0
#define PIN_ESP_BOOT PA1
#define PIN_ESP_TX PA2   
#define PIN_ESP_RX PA3  
static constexpr uint32_t ESP_LINK_BAUD = 115200;

// Sensor
#define PIN_SENS_SCK PB13
#define PIN_SENS_MISO PB14
#define PIN_SENS_MOSI PB15
#define PIN_IMU_CS PA9
#define PIN_BARO_CS PB12
#define PIN_IMU_INT1 PA8
#define PIN_IMU_INT2 PC9
#define PIN_BARO_INT PB11

// Magnetometer
#define PIN_MAG_SDA PB7
#define PIN_MAG_SCL PA15
static constexpr uint8_t MMC5603_ADDR = 0x30;

// Motor Driver
#define PIN_M_INHA PC6 
#define PIN_M_INHB PC7
#define PIN_M_INHC PC8 
#define PIN_M_INLA PC10
#define PIN_M_INLB PC11
#define PIN_M_INLC PC12
#define PIN_M_NSLEEP PA4
#define PIN_M_NFAULT PB5
#define PIN_M_SOA PA6
#define PIN_M_SOB PA7
#define PIN_M_SOC PB1

// Servo
#define PIN_SERVO      PB4

// HMI
#define PIN_STATUS_LED PB6
#define PIN_LED_ARRAY PC4
#define PIN_BUZZER PC5
static constexpr uint16_t LED_ARRAY_COUNT = 4;

// Power
#define PIN_VMON PB0
#define PIN_USB_VBUS PA10
static constexpr float VBAT_DIVIDER = 2.0f;
static constexpr float ADC_VREF = 3.3f;

// 1S LiPo
static constexpr float VBAT_WARN = 3.60f;
static constexpr float VBAT_CRITICAL = 3.40f;

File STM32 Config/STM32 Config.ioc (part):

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Mcu.Name=STM32G473R(B-C-E)Tx
Mcu.Package=LQFP64
Mcu.UserName=STM32G473RCTx
PA0.Signal=GPIO_Output
PA1.Signal=GPIO_Output
PA10.Signal=GPIO_Input
PA11.Mode=Device
PA11.Signal=USB_DM
PA12.Mode=Device
PA12.Signal=USB_DP
PA13.Signal=SYS_JTMS-SWDIO
PA14.Signal=SYS_JTCK-SWCLK
PA15.Signal=I2C1_SCL
PA2.Signal=USART2_TX
PA3.Signal=USART2_RX
PA5.Signal=ADC2_IN13
PA6.Signal=ADC2_IN3
PA8.Signal=GPIO_Output
PA9.Signal=GPIO_Input
PB0.Signal=ADC1_IN15
PB1.Mode=IN1-Single-Ended
PB1.Signal=ADC3_IN1
PB11.Signal=GPIO_Output
PB12.Signal=GPIO_Input
PB13.Signal=SPI2_SCK
PB14.Signal=SPI2_MISO
PB15.Signal=SPI2_MOSI
PB2.Signal=I2C3_SMBA
PB3.Signal=SYS_JTDO-SWO
PB4.Signal=GPXTI4
PB5.Signal=GPIO_Output
PB6.Signal=TIM8_BKIN2
PB7.Signal=I2C1_SDA
PB8-BOOT0.Signal=GPIO_Input
PC10.Signal=TIM8_CH1N
PC11.Signal=TIM8_CH2N
PC12.Signal=TIM8_CH3N
PC2.Signal=GPIO_Output
PC3.Signal=GPIO_Output
PC4.Signal=GPIO_Output
PC5.Signal=GPIO_Output
PC6.Signal=S_TIM8_CH1
PC7.Signal=S_TIM8_CH2
PC8.Signal=S_TIM8_CH3
PC9.Signal=GPIO_Output
PG10-NRST.Signal=GPIO_Output
RCC.HSE_VALUE=8000000
RCC.SYSCLKFreq_VALUE=16000000
board=custom

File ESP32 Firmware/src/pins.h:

#pragma once
#include <Arduino.h>

// UWB 
static constexpr int PIN_DW_WAKEUP = 1;
static constexpr int PIN_DW_IRQ = 3;
static constexpr int PIN_DW_MISO = 4;
static constexpr int PIN_DW_MOSI = 5;
static constexpr int PIN_DW_CLK = 6;
static constexpr int PIN_DW_CS = 7;
static constexpr int PIN_DW_RST = 10;

// Magnetometer
static constexpr int PIN_MAG_SDA = 18;
static constexpr int PIN_MAG_SCL = 19;
static constexpr uint8_t MMC5603_ADDR = 0x30;

// STM32 Link
static constexpr int PIN_LINK_RX = 20;
static constexpr int PIN_LINK_TX = 21;
static constexpr uint32_t LINK_BAUD = 115200;

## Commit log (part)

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2026-06-22 init
2026-06-23 sync
